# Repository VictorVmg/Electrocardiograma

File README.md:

# Electrocardiograma    
El diseño cuenta con un integrado ADS1292R el cual brinda la capacidad de monitorear la respiración del usuario. Además, se añaden al proyecto una etapa de pruebas la cual hace posible la conexión paciente dispositivo.

## Repositorio

En las carpetas del repositorio se encuentran todos los documentos asociados y que fueron necesarios para realizar este proyecto, entre otras cosas mas.

## Descripción del proyecto 
El proyecto consiste en la creación de un electrocardiograma el cual tenga un tamaño perfecto para el dia a dia del usuario, pequeño, ligero y seguro. Adicionalmente cuenta con un Display OLED el cual permite al usuario monitorear su estado actual asi como el del equipo. El Electrocardiograma cuenta con la compatibilidad de mikro bus el cual expande el potencial de dicho equipo, haciendo que el mismo sea posible ser usado en consultas a distancias y monitoreo profesional por parte del cardiologo que lleve el caso del usuario.

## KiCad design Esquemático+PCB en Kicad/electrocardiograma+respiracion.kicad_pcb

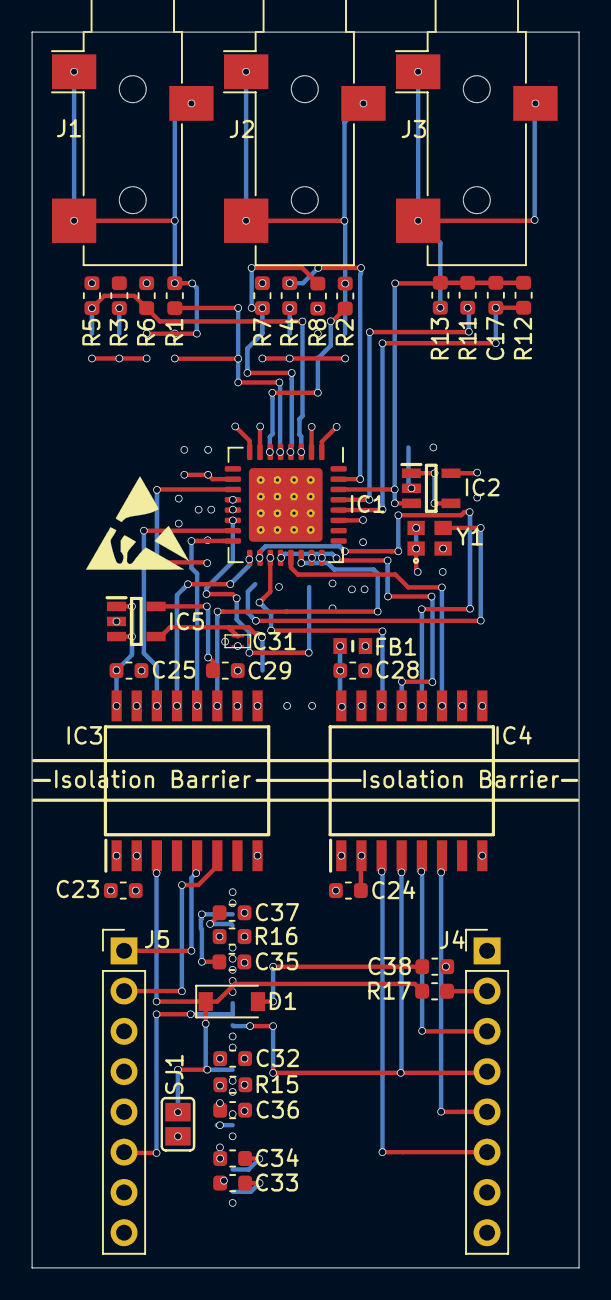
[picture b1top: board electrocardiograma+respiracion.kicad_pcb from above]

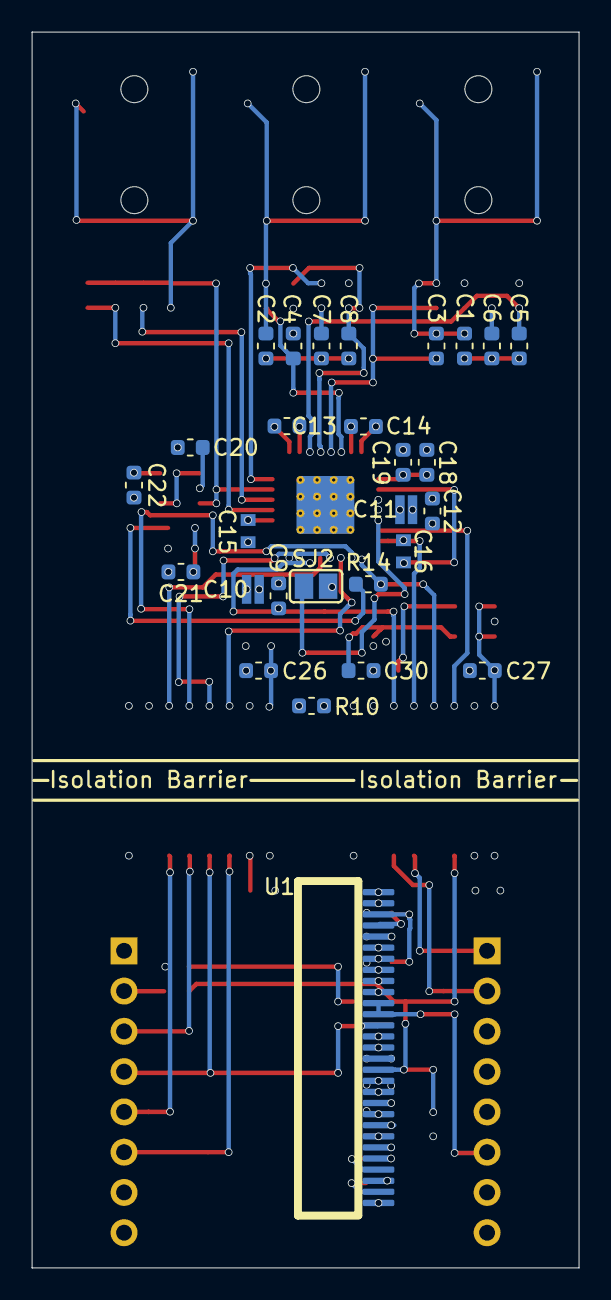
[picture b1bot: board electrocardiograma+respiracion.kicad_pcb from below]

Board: 4 copper layers, 34.5 x 78.0 mm, 70 parts (28 on the bottom side), 63 nets.

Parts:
C1, C2: 0.1uf; C_0603_1608Metric
C3, C4: 3nF; C_0603_1608Metric
C5, C6, C7, C8: 2.2nF; C_0603_1608Metric
C9, C12, C18, C20, C21, C22: 0.1uF; C_0603_1608Metric
C10, C11: 1uF; capacitor invertido
C13, C14: 47nF; C_0603_1608Metric
C15, C16: 1uF; capacitor C0G
C17: C_Small; C_0603_1608Metric
C19, C23, C24, C25, C26, C35: 10uF; C_0603_1608Metric
C27, C28, C30, C32, C33, C34, C36: 1uF; C_0603_1608Metric
C29: 10nF; C_0603_1608Metric
C31: 1uF_EMIFIL; NFM18PS
C37: 2.2uF/16V; C_0603_1608Metric
C38: 4.7uF; C_0603_1608Metric
D1: 1N4148W; D_SOD-123
FB1: BLM18PG121SZ1D
IC1: ADS1292RIPBS-SamacSys_Parts; QFN-32-1EP_7x7mm_P0.65mm_EP4.65x4.65mm_ThermalVias
IC2: OPA197; OPAMP197IDBVR
IC3: ISOW7842DWER-SamacSys_Parts; ISOW7841FDWER
IC4: ISOW7841FDWER-SamacSys_Parts; ISOW7841FDWER
IC5: LP3985IM5-3.0_NOPB-SamacSys_Parts; LP3985IM5-3.0_NOPB
J1, J2, J3: AudioJack3; Jack_3.5mm_CUI_SJ-3523-SMT_Horizontal
J4, J5: Conn_01x08; PinHeader_1x08_P2.54mm_Vertical
R1, R2: 51.1K; R_0603_1608Metric
R3, R4: 40.2K; R_0603_1608Metric
R5, R6, R7, R8: 10M; R_0603_1608Metric
R10, R14: 0; R_0603_1608Metric
R11, R13: 100K; R_0603_1608Metric
R12: 1M; R_0603_1608Metric
R15: 10K; R_0603_1608Metric
R16: 390K; R_0603_1608Metric
R17: 1K; R_0603_1608Metric
SJ1, SJ2: JUMPER; SOLDERJUMPER_REFLOW_NOPASTE
U1: UG-2864HSWEG01; display
Y1: SG-210STF_40.0000ML3; oscilator

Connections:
+3V3: C23.1, C24.2, C32.1, C36.2, IC3.1, IC4.1, J4.7, R15.2, U1.6, U1.7, U1.9, U1.11
ADRDY: IC1.22, IC3.11
ARESET: IC1.15, IC3.14
CLK: IC1.17, IC3.13, R14.1
CLKSEL: IC1.14, SJ2.1
CS: IC4.5, J4.3
DRDY: IC3.6, J5.2
ELA: C2.2, J2.R, J2.S, J2.T, R2.2
ERA: C1.2, J1.R, J1.S, J1.T, R1.2
GND: C23.2, C24.1, C32.2, C35.1, C36.1, C37.1, C38.2, IC3.2, IC3.8, IC4.2, IC4.8, J4.8, J5.8, R15.1, R16.2, SJ1.2, U1.1, U1.8, U1.10, U1.12, U1.13, U1.16, U1.17, U1.21, U1.22, U1.23, U1.24, U1.25, U1.29, U1.30
GNDA: C3.2, C4.2, C11.2, C12.2, C15.2, C16.2, C18.1, C19.1, C20.2, C21.2, C22.2, C25.1, C27.2, C29.2, C30.2, C31.2, IC1.12, IC1.13, IC3.9, IC3.10, IC3.15, IC5.2, R6.2, R8.1, R10.2, SJ2.2, Y1.2
GNDD: C9.2, C10.2, C26.1, C28.2, IC1.23, IC1.24, IC4.9, IC4.10, IC4.15, R10.1
IN1N: C5.1, IC1.3, R5.2, R6.1
IN1P: C8.1, IC1.4, R7.1, R8.2
IN2N: C3.1, IC1.5, R1.1
IN2P: C4.1, IC1.6, R2.1
MISO: IC4.6, J4.5
MOSI: IC4.3, J4.6
unnamed: C1.1, C5.2, C6.2
unnamed: C2.1, C7.2, C8.2
unnamed: C6.1, R3.2
unnamed: C7.1, R4.2
unnamed: C13.1, IC1.1
unnamed: C13.2, IC1.2
unnamed: C14.1, IC1.7
unnamed: C14.2, IC1.8
unnamed: C15.1, IC1.27
unnamed: C16.1, IC1.11
unnamed: C17.1, IC1.28, R12.2
unnamed: C17.2, IC1.30, IC2.3, R11.1, R12.1, R13.2
unnamed: C18.2, C19.2, IC1.10
unnamed: C20.1, IC2.2
unnamed: C21.1, Y1.1, Y1.4
unnamed: C22.1, IC2.5
unnamed: C25.2, C27.1, IC3.16, IC5.1, IC5.3
unnamed: C26.2, C28.1, FB1.1, IC4.16
unnamed: C29.1, IC5.5
unnamed: C30.1, C31.1, IC5.4
unnamed: C33.1, U1.2
unnamed: C33.2, U1.3
unnamed: C34.1, U1.4
unnamed: C34.2, U1.5
unnamed: C35.2, U1.28
unnamed: C37.2, U1.27
unnamed: C38.1, D1.2
unnamed: IC1.29, R11.2
unnamed: IC2.1, IC2.4
unnamed: R14.2, Y1.3
unnamed: R16.1, U1.26
RESP_MODP_IN3P: IC1.31, R4.1
RLD: J3.R, J3.S, J3.T, R13.1
RST: D1.1, IC3.3, R17.2, SJ1.1, U1.14
RST-Warp7: J4.2, R17.1
SCK: IC4.4, J4.4, U1.18
SDA: J5.6, U1.19, U1.20
SPI_ACS: IC1.18, IC4.12
SPI_ADIN: IC1.19, IC4.14
SPI_ADOUT: IC1.21, IC4.11
SPI_ASCLK: IC1.20, IC4.13
START: IC1.16, IC3.12
STARTB: IC3.5, J5.1
VDD: C9.1, C10.1, FB1.2
VDDA: C11.1, C12.1, C31.3, R5.1, R7.2

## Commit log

2019-10-13 Create Documentos
2019-10-15 Create temporal
2019-10-15 documentación
    Estos documentos son los necesarios para la operación del circuito. Entre ellos, están los data sheet de los componentes que se consideraron óptimos para la creación del Electrocardiograma.
2019-10-15 Imagenes
    En las Imagenes se encuentra:
    -Conexiones de los tres electrodos
    -Esquemático para Arduino
    -Vista frontal 3D del pcd
    -Vista trasera del
2019-10-15 Create txt
2019-10-15 Librerias
    Las librerias son para el uso en kicad
2019-10-15 Esquemáticos mas PCB
    en esta carpeta se encuentran los esquemáticos de:
    - Protecciones
    - Pantalla
    - ADS1292R
    -Extras
2019-10-15 archivos principales
    Esquemáticos, pcb de cuatro (4) capas con sus vistas 3D.
